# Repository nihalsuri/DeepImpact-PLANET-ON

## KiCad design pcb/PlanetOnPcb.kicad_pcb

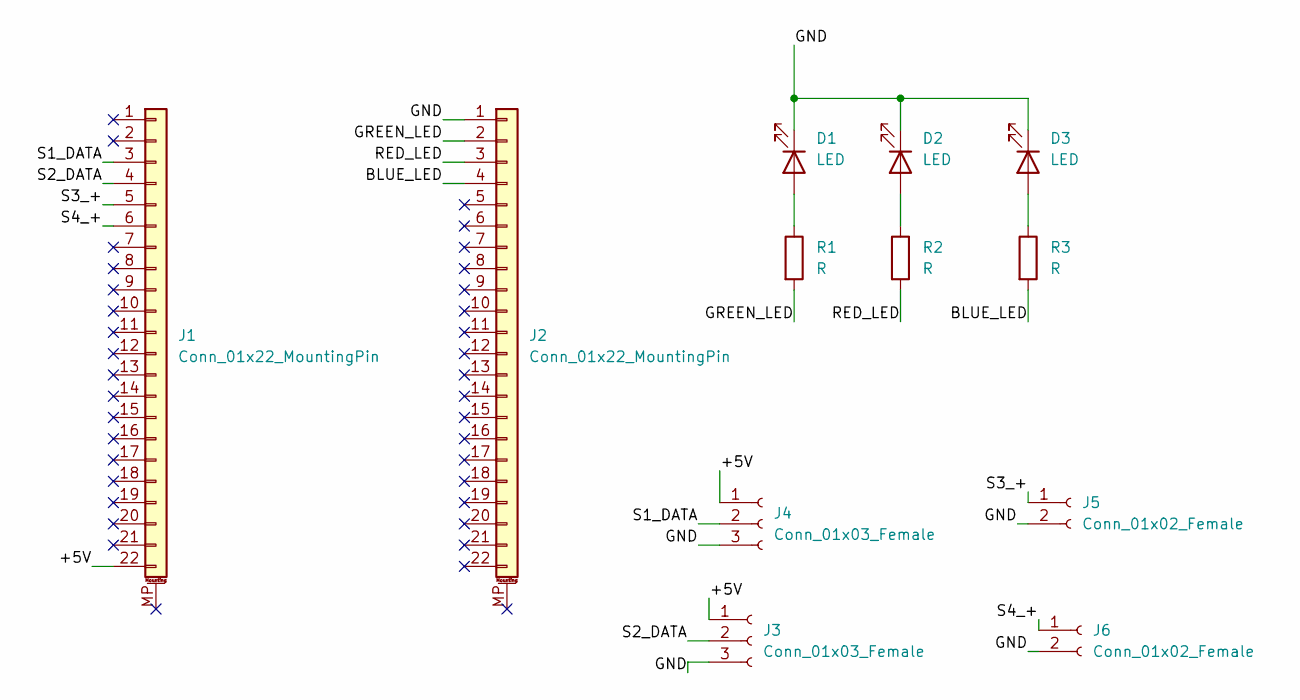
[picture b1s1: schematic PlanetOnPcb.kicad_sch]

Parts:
D1, D2, D3: LED; LED_D3.0mm_FlatTop
J1, J2: Conn_01x22_MountingPin; PinSocket_1x22_P1.27mm_Vertical
J3, J4: Conn_01x03_Female; PinSocket_1x03_P1.27mm_Vertical
J5, J6: Conn_01x02_Female; PinSocket_1x02_P1.27mm_Vertical
R1, R2, R3: R; R_0201_0603Metric

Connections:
/+5V: J1.22, J3.1, J4.1
/BLUE_LED: J2.4, R3.2
/GND: D1.1 (K), D2.1 (K), D3.1 (K), J2.1, J3.3, J4.3, J5.2, J6.2
/GREEN_LED: J2.2, R1.2
/RED_LED: J2.3, R2.2
/S1_DATA: J1.3, J4.2
/S2_DATA: J1.4, J3.2
/S3_+: J1.5, J5.1
/S4_+: J1.6, J6.1
unnamed: D1.2 (A), R1.1
unnamed: D2.2 (A), R2.1
unnamed: D3.2 (A), R3.1

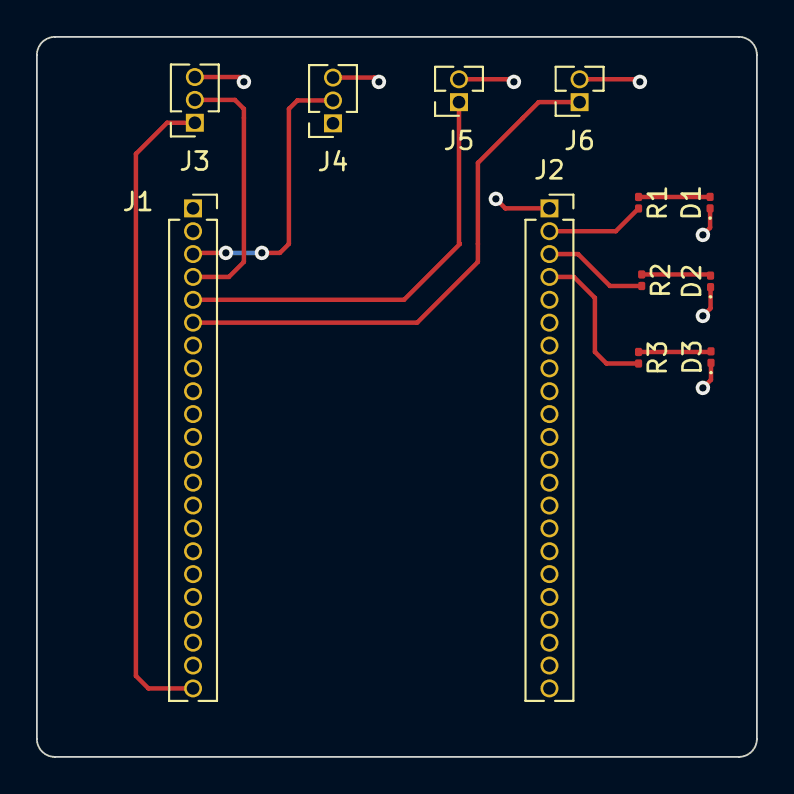
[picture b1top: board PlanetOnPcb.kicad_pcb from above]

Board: 2 copper layers, 40.0 x 40.0 mm, 12 parts (0 on the bottom side), 12 nets.

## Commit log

2022-11-19 initial commit, mqtt works
2022-11-19 added git ignore
2022-11-20 removed readme
2022-11-20 Added final files
2022-11-20 Added cad and PCB
